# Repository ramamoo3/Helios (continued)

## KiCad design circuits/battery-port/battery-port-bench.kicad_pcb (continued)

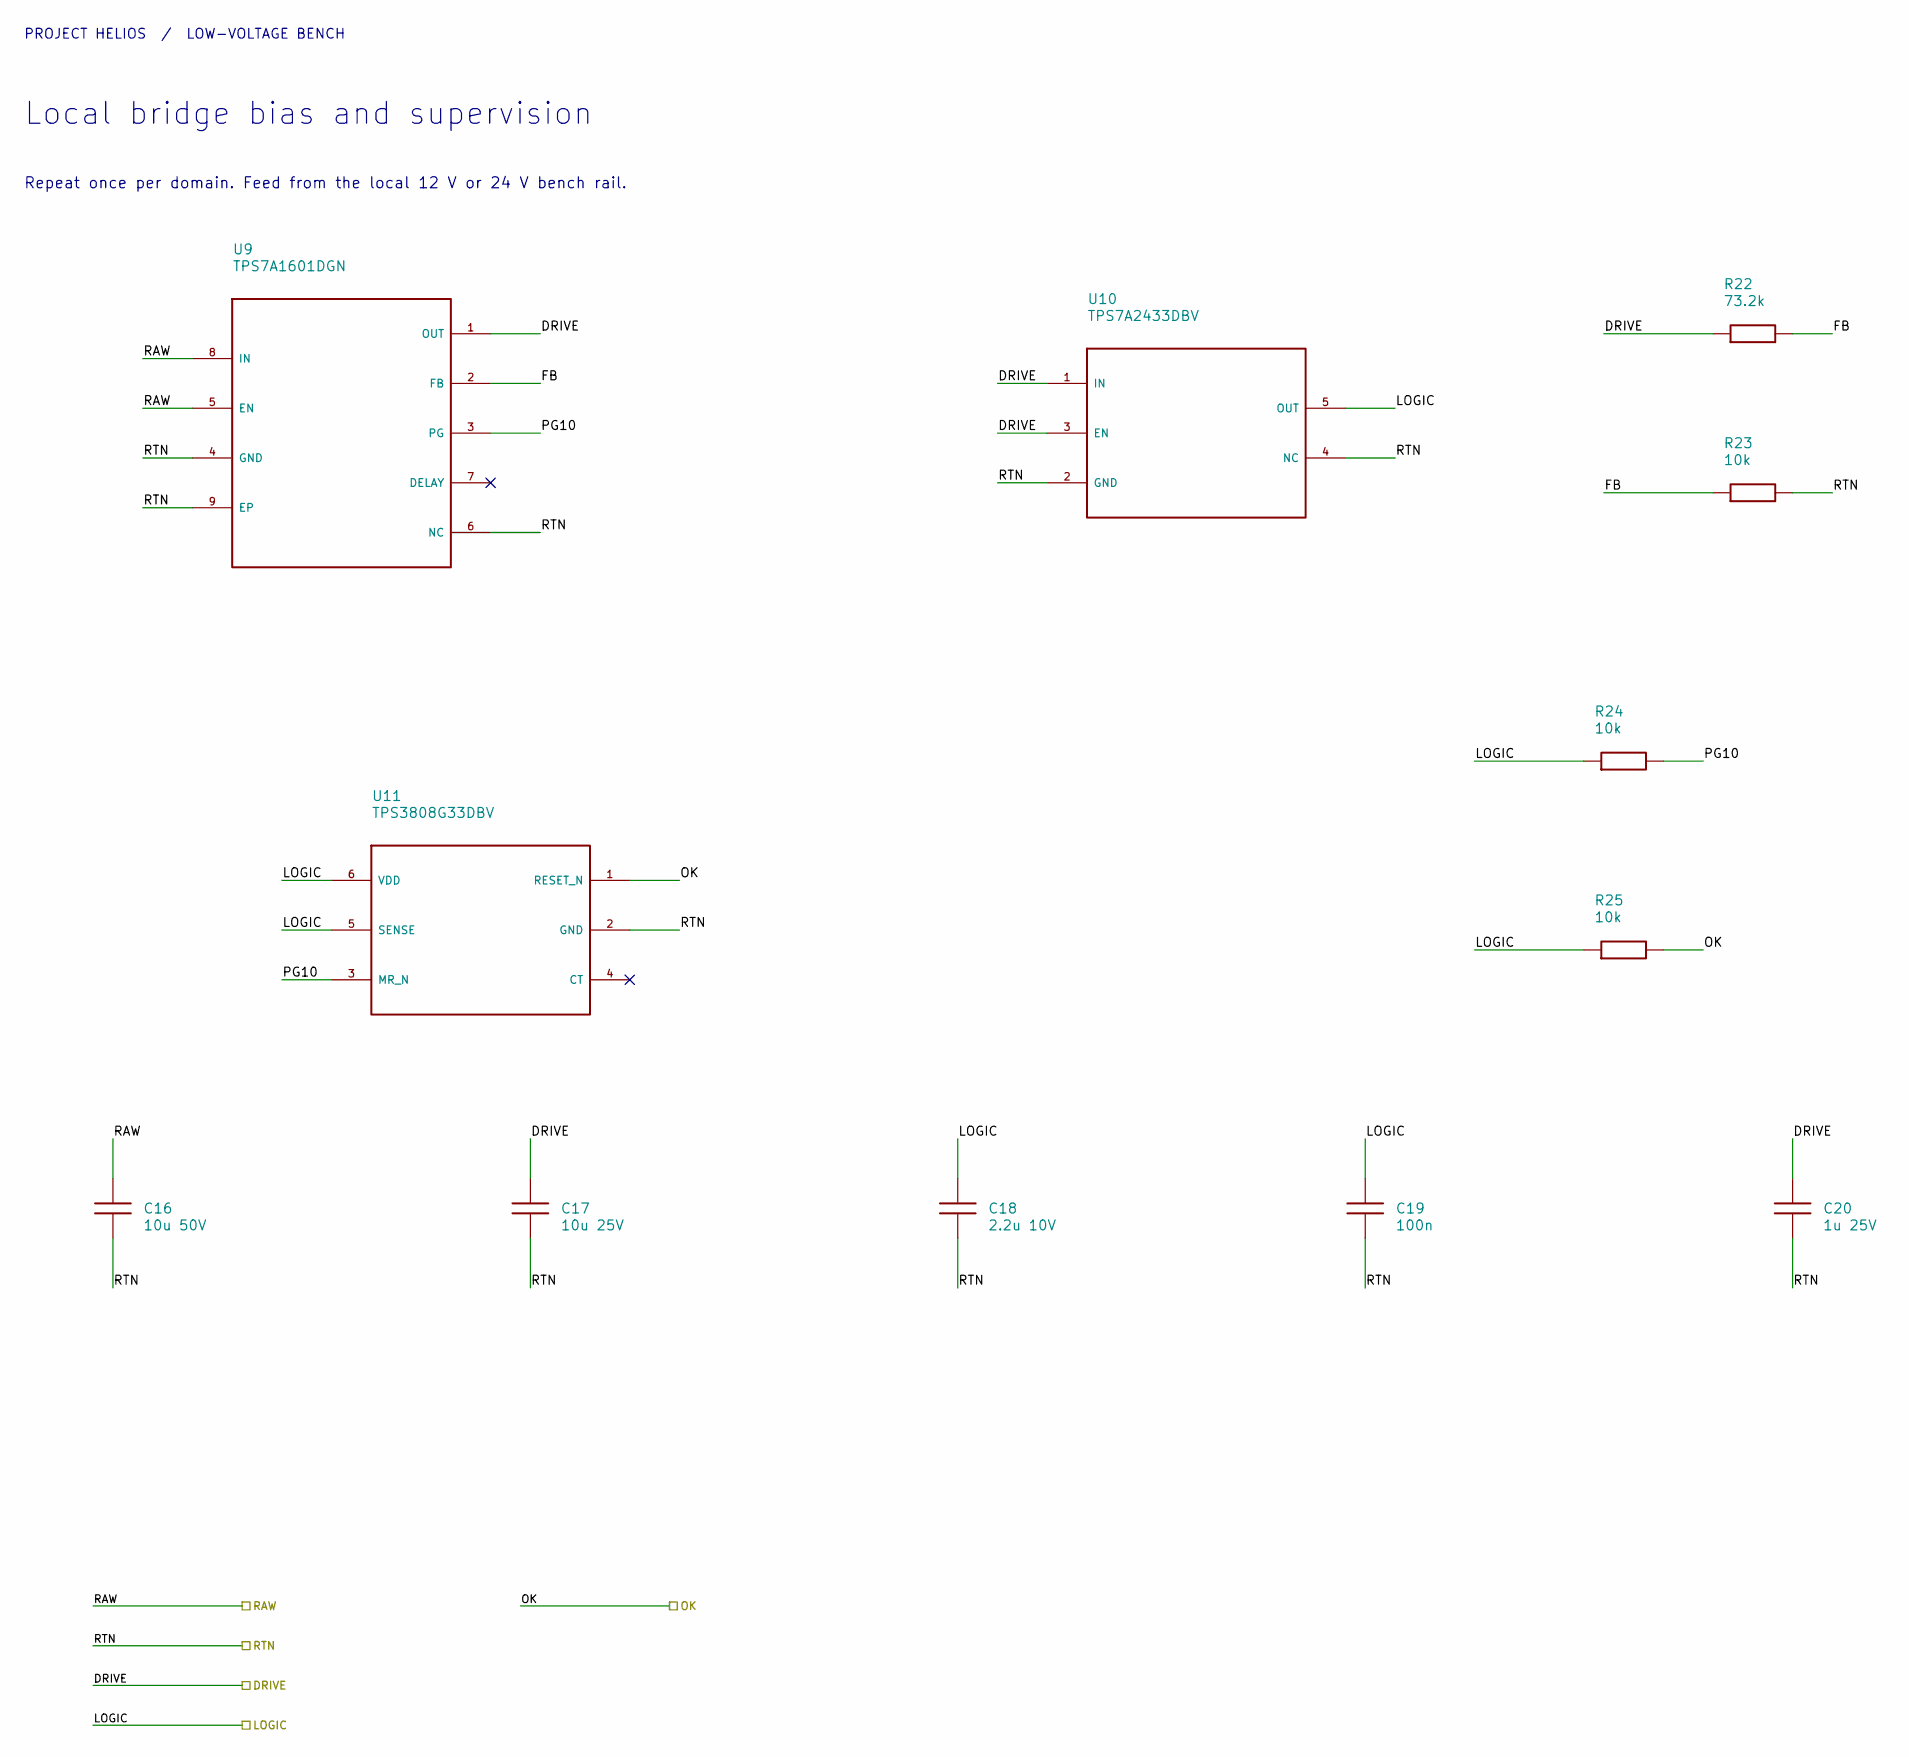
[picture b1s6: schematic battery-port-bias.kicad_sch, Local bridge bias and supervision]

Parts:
C16: 10u 50V; C_1206_3216Metric
C17: 10u 25V; C_1206_3216Metric
C18: 2.2u 10V; C_1206_3216Metric
C19: 100n; C_0805_2012Metric; Voltage Rating 50 V; MPN CGA4J2X8R1H104K125AA
C20: 1u 25V; C_0805_2012Metric
R22: 73.2k; R_0805_2012Metric
R23, R24, R25: 10k; R_0805_2012Metric
U9: TPS7A1601DGN; TI_DGN0008C
U10: TPS7A2433DBV; SOT-23-5
U11: TPS3808G33DBV; SOT-23-6

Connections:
/P0: C16.2, C17.2, C18.2, C19.2, C20.2, R23.2, U9.4 (GND), U9.6 (NC), U9.9 (EP), U10.2 (GND), U10.4 (NC), U11.2 (GND); also elsewhere on the board
/P3V3: C18.1, C19.1, R24.1, R25.1, U10.5 (OUT), U11.5 (SENSE), U11.6 (VDD); also elsewhere on the board
/P10: C17.1, C20.1, R22.1, U9.1 (OUT), U10.1 (IN), U10.3 (EN); also elsewhere on the board
/PACK12: C16.1, U9.5 (EN), U9.8 (IN); also elsewhere on the board
/PRI_OK: R25.2, U11.1 (RESET_N); also elsewhere on the board
/Primary bias/FB: R22.2, R23.1, U9.2 (FB)
/Primary bias/PG10: R24.2, U9.3 (PG), U11.3 (MR_N)

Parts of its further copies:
C116: 10u 50V; C_1206_3216Metric
C117: 10u 25V; C_1206_3216Metric
C118: 2.2u 10V; C_1206_3216Metric
C119: 100n; C_0805_2012Metric; Voltage Rating 50 V; MPN CGA4J2X8R1H104K125AA
C120: 1u 25V; C_0805_2012Metric
R122: 73.2k; R_0805_2012Metric
R123, R124, R125: 10k; R_0805_2012Metric
U109: TPS7A1601DGN; TI_DGN0008C
U110: TPS7A2433DBV; SOT-23-5
U111: TPS3808G33DBV; SOT-23-6

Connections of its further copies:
/LINK24: C116.1, U109.5 (EN), U109.8 (IN); also elsewhere on the board
/S0: C116.2, C117.2, C118.2, C119.2, C120.2, R123.2, U109.4 (GND), U109.6 (NC), U109.9 (EP), U110.2 (GND), U110.4 (NC), U111.2 (GND); also elsewhere on the board
/S3V3: C118.1, C119.1, R124.1, R125.1, U110.5 (OUT), U111.5 (SENSE), U111.6 (VDD); also elsewhere on the board
/S10: C117.1, C120.1, R122.1, U109.1 (OUT), U110.1 (IN), U110.3 (EN); also elsewhere on the board
/SEC_OK: R125.2, U111.1 (RESET_N); also elsewhere on the board
/Secondary bias/FB: R122.2, R123.1, U109.2 (FB)
/Secondary bias/PG10: R124.2, U109.3 (PG), U111.3 (MR_N)

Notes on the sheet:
PROJECT HELIOS / LOW-VOLTAGE BENCH
Local bridge bias and supervision
Repeat once per domain. Feed from the local 12 V or 24 V bench rail.

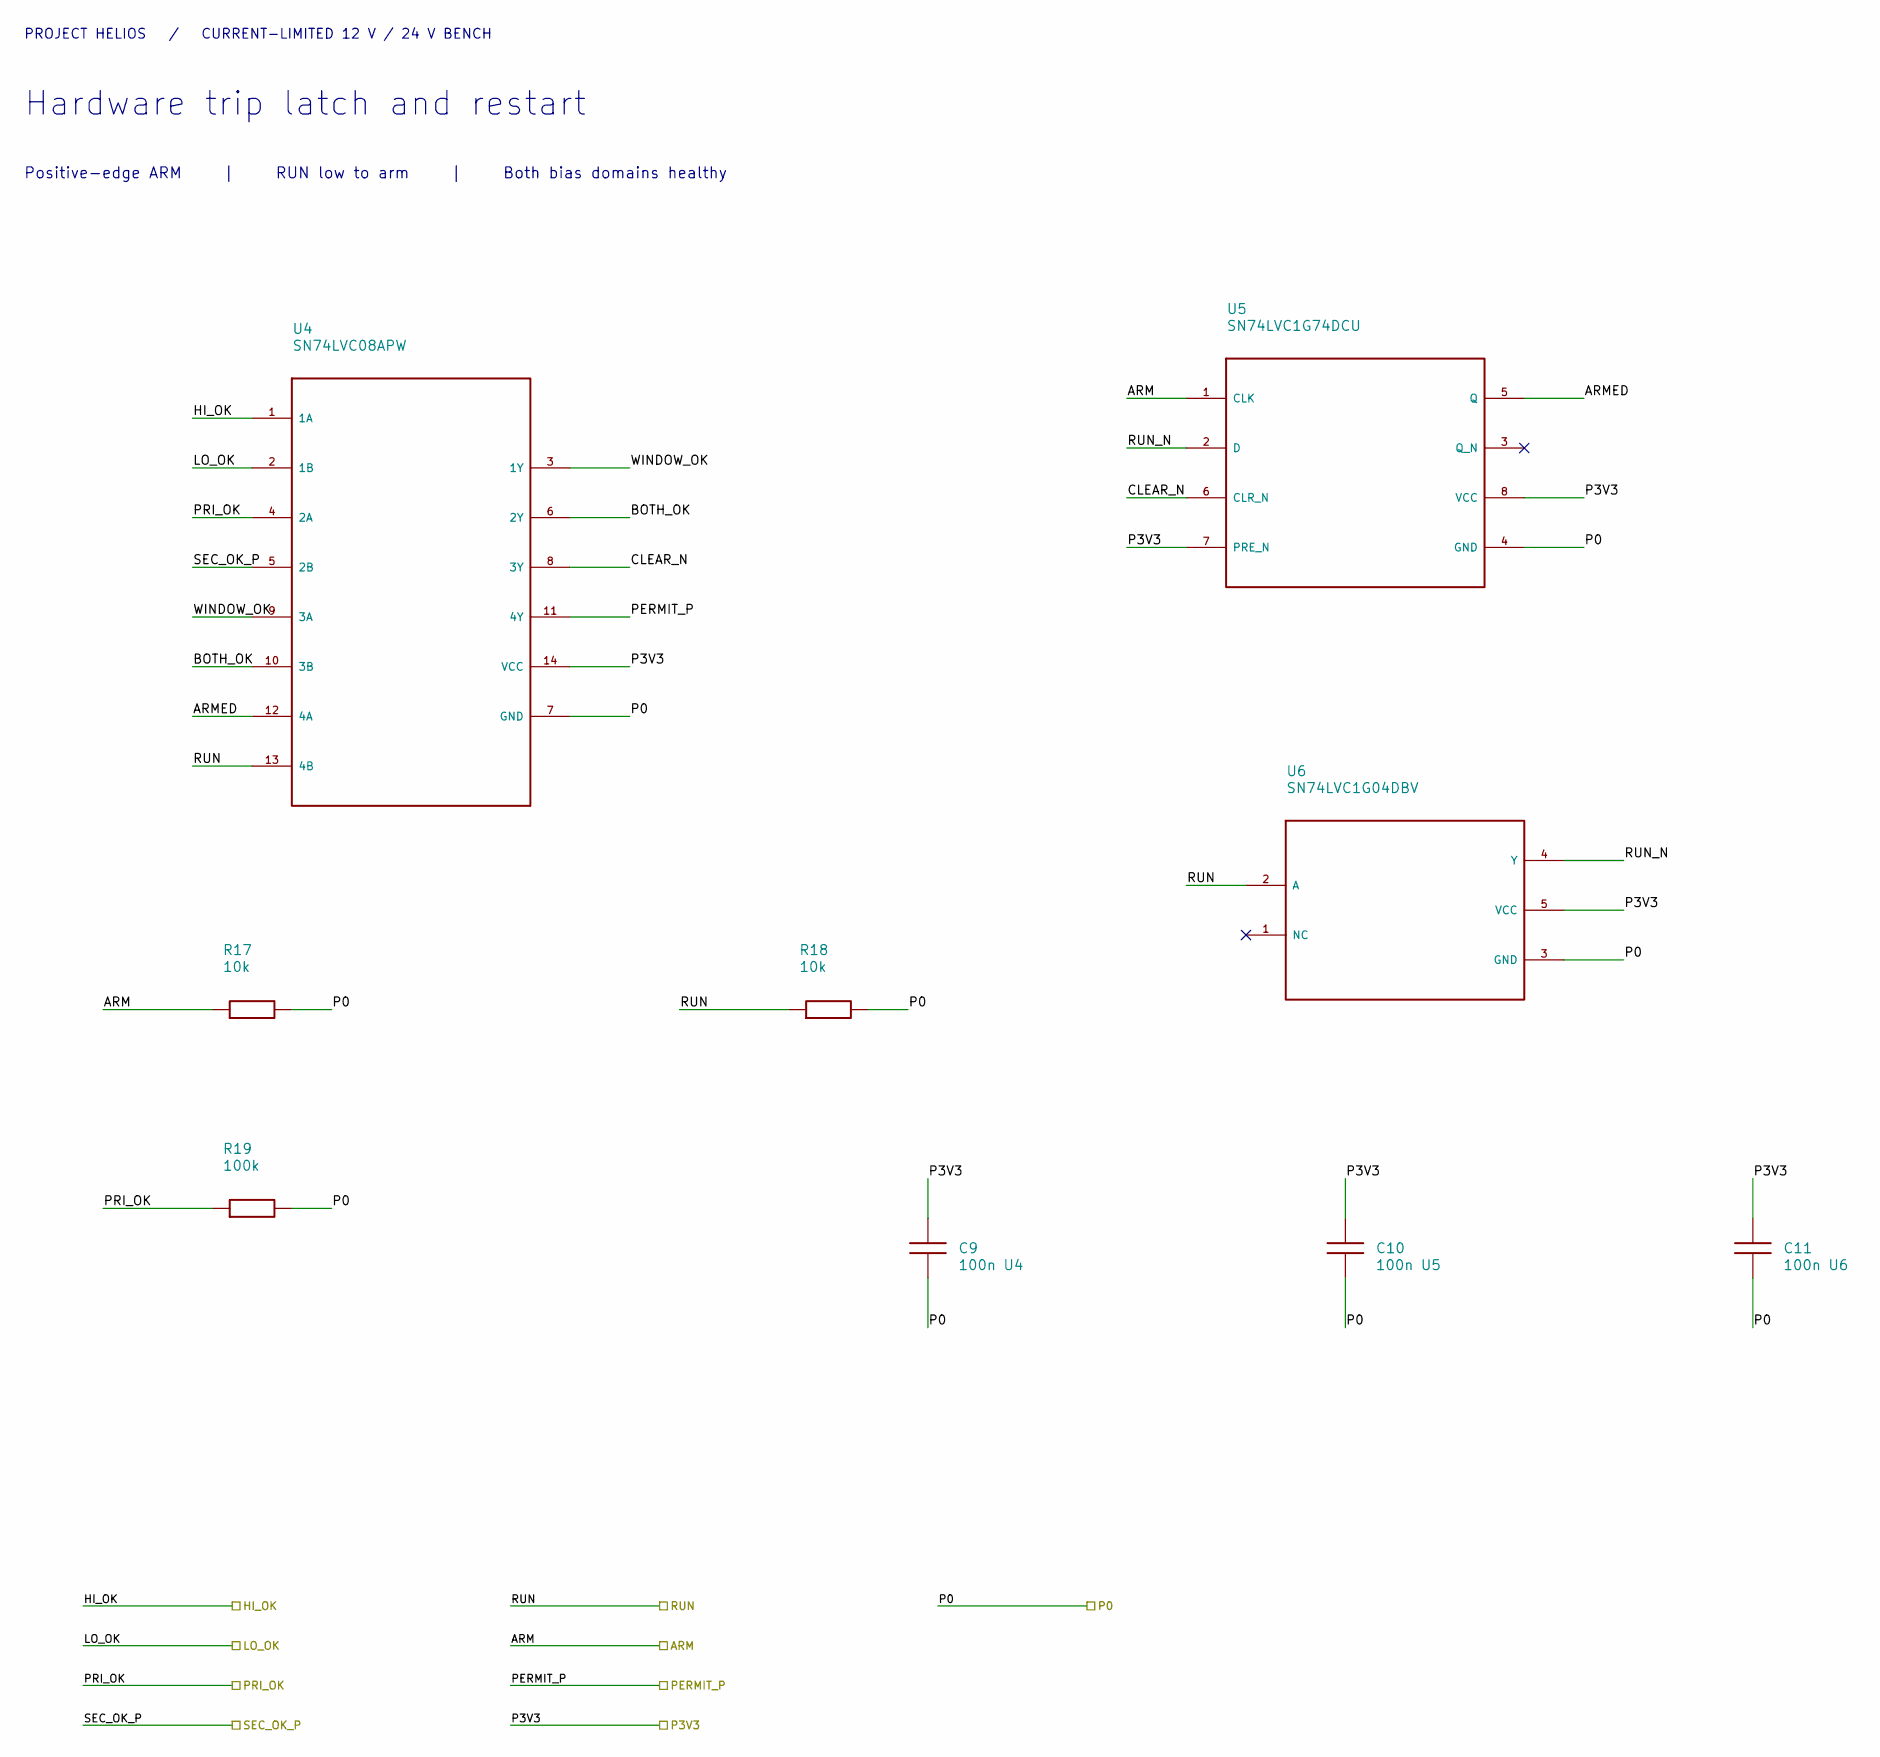
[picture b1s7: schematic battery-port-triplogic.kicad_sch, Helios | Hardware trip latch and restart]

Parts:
C9: 100n U4; C_0805_2012Metric
C10: 100n U5; C_0805_2012Metric
C11: 100n U6; C_0805_2012Metric
R17, R18: 10k; R_0805_2012Metric
R19: 100k; R_0805_2012Metric
U4: SN74LVC08APW; TSSOP-14_4.4x5mm_P0.65mm
U5: SN74LVC1G74DCU; TI_DCU0008A
U6: SN74LVC1G04DBV; SOT-23-5

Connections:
/ARM: R17.1, U5.1 (CLK); also elsewhere on the board
/HI_OK: U4.1 (1A); also elsewhere on the board
/LO_OK: U4.2 (1B); also elsewhere on the board
/Latch and re-arm/ARMED: U4.12 (4A), U5.5 (Q)
/Latch and re-arm/BOTH_OK: U4.6 (2Y), U4.10 (3B)
/Latch and re-arm/CLEAR_N: U4.8 (3Y), U5.6 (CLR_N)
/Latch and re-arm/RUN_N: U5.2 (D), U6.4 (Y)
/Latch and re-arm/WINDOW_OK: U4.3 (1Y), U4.9 (3A)
/P0: C9.2, C10.2, C11.2, R17.2, R18.2, R19.2, U4.7 (GND), U5.4 (GND), U6.3 (GND); also elsewhere on the board
/P3V3: C9.1, C10.1, C11.1, U4.14 (VCC), U5.7 (PRE_N), U5.8 (VCC), U6.5 (VCC); also elsewhere on the board
/PERMIT_P: U4.11 (4Y); also elsewhere on the board
/PRI_OK: R19.1, U4.4 (2A); also elsewhere on the board
/RUN: R18.1, U4.13 (4B), U6.2 (A); also elsewhere on the board
/SEC_OK_P: U4.5 (2B); also elsewhere on the board

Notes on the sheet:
PROJECT HELIOS / CURRENT-LIMITED 12 V / 24 V BENCH
Hardware trip latch and restart
Positive-edge ARM | RUN low to arm | Both bias domains healthy

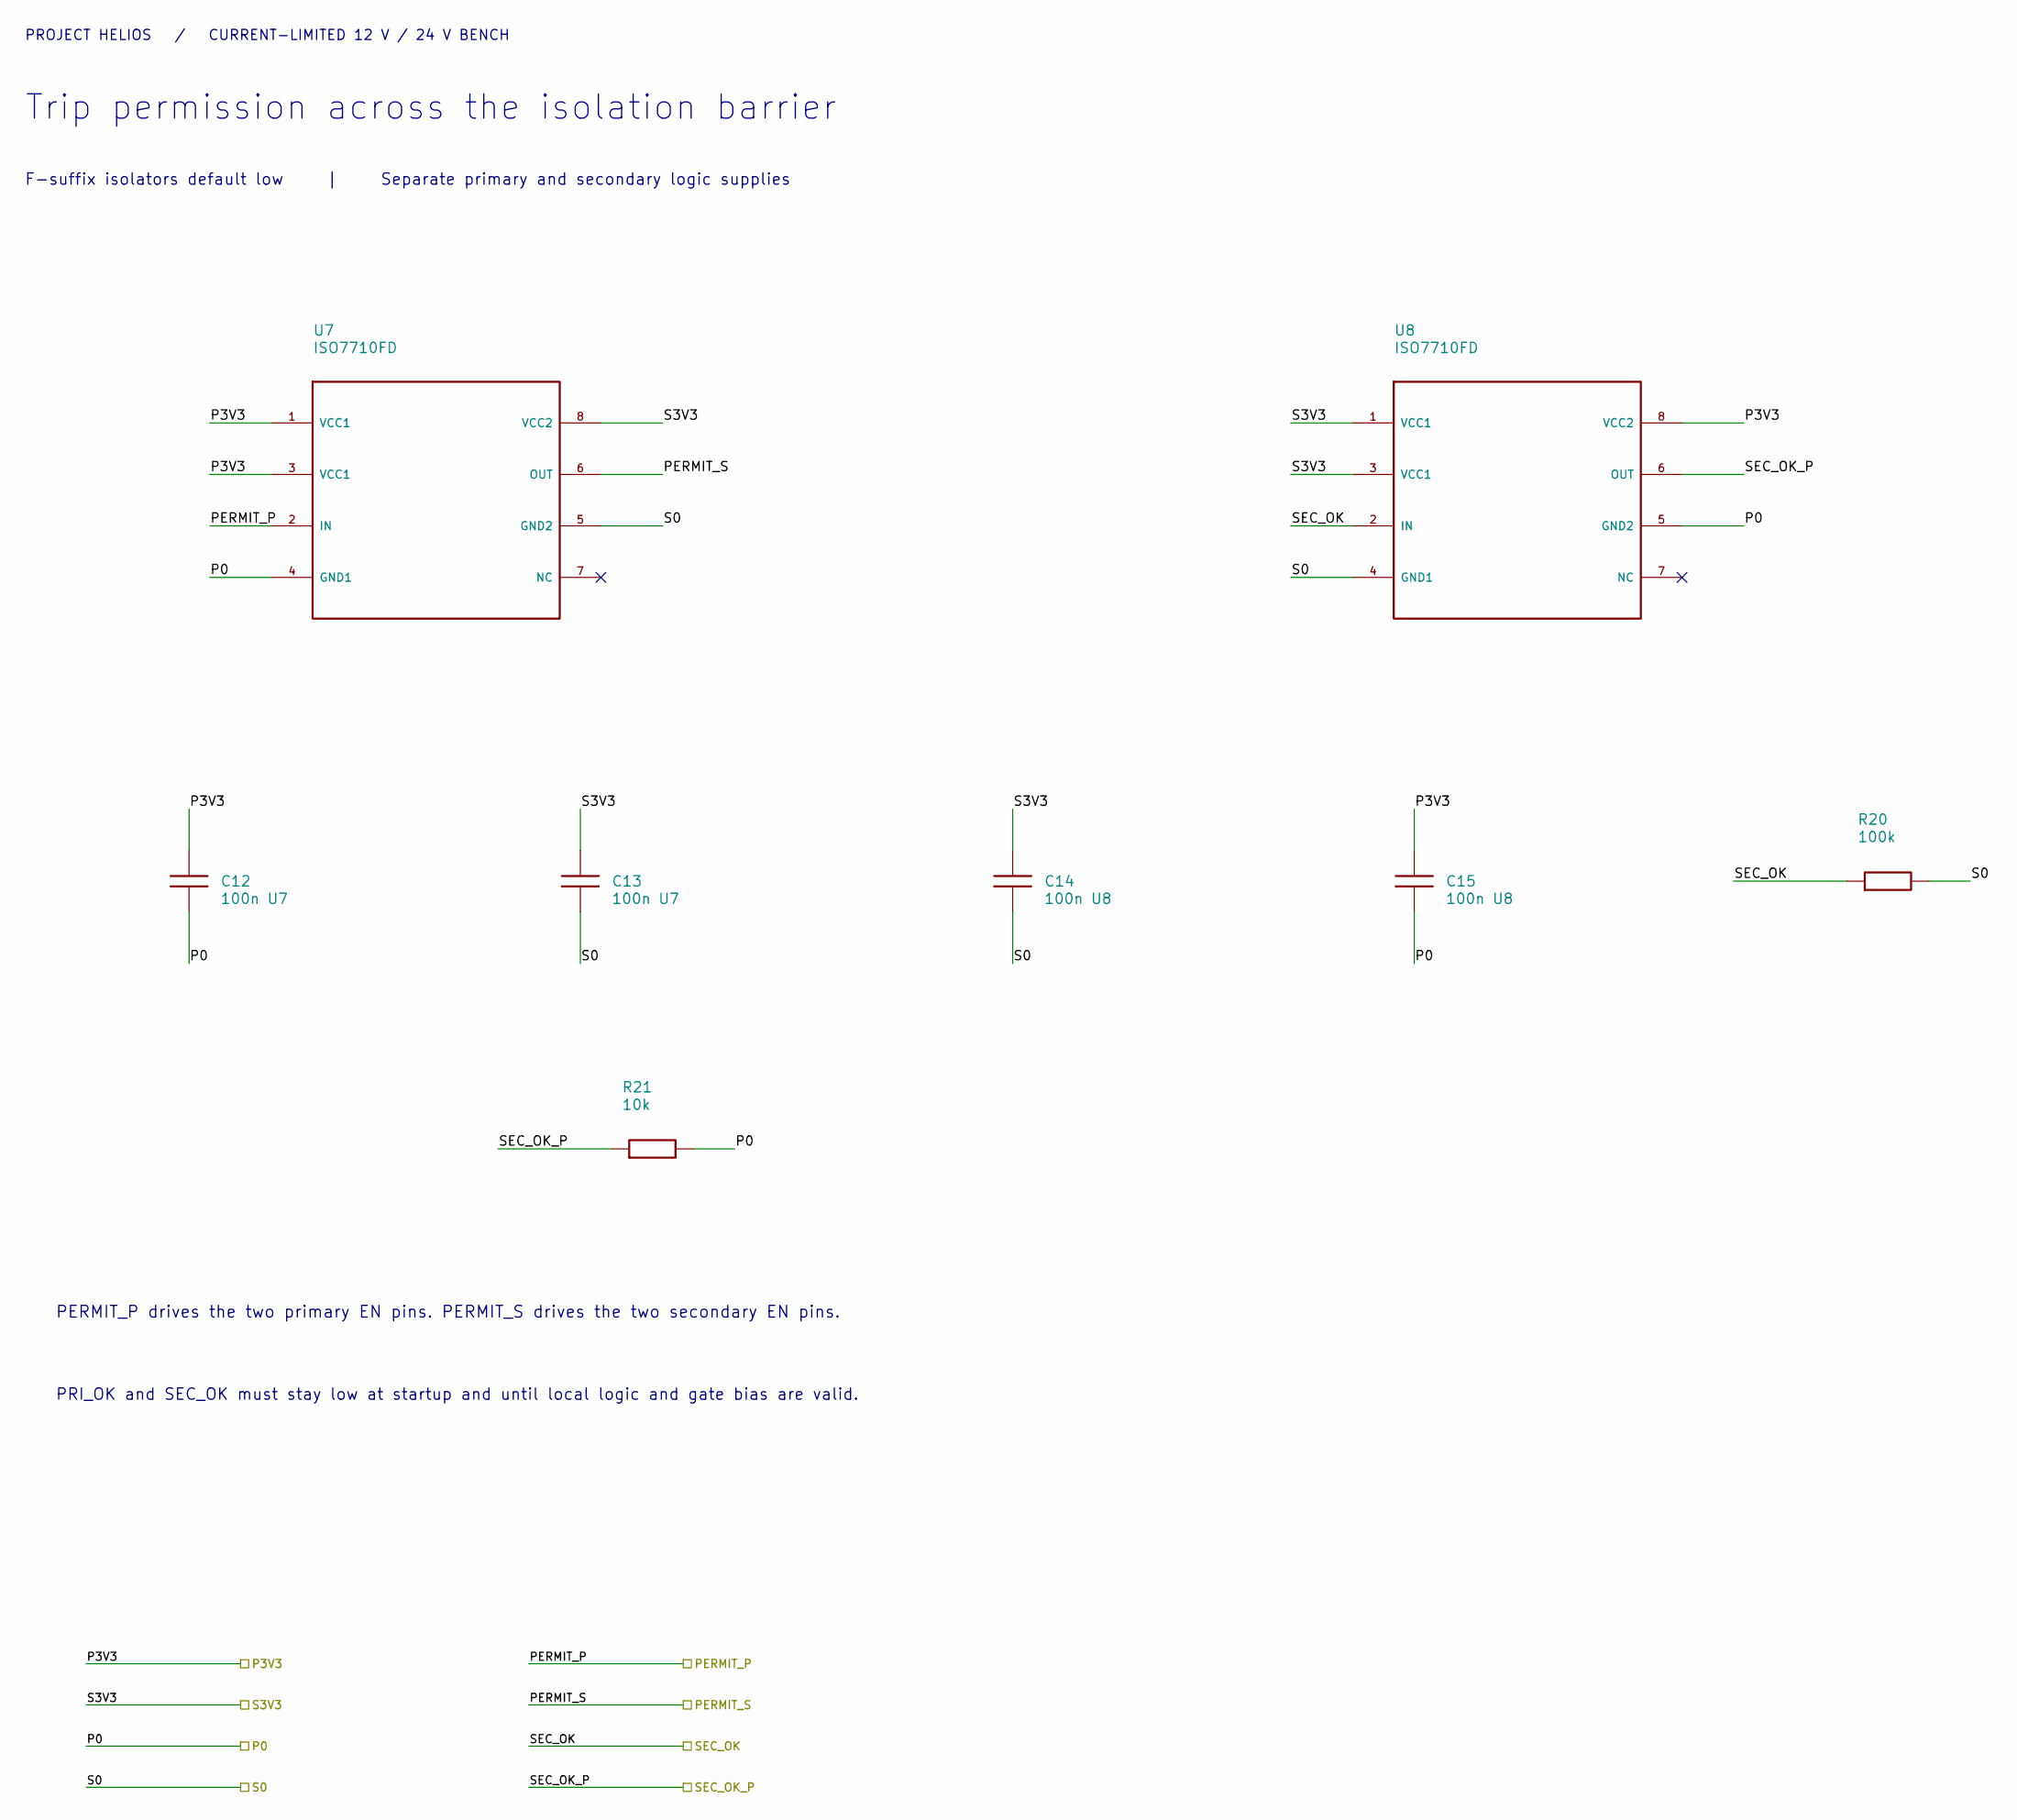
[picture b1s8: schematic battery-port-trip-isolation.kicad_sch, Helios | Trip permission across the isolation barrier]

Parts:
C12, C13: 100n U7; C_0805_2012Metric
C14, C15: 100n U8; C_0805_2012Metric
R20: 100k; R_0805_2012Metric
R21: 10k; R_0805_2012Metric
U7, U8: ISO7710FD; SOIC-8_3.9x4.9mm_P1.27mm

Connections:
/P0: C12.2, C15.2, R21.2, U7.4 (GND1), U8.5 (GND2); also elsewhere on the board
/P3V3: C12.1, C15.1, U7.1 (VCC1), U7.3 (VCC1), U8.8 (VCC2); also elsewhere on the board
/PERMIT_P: U7.2 (IN); also elsewhere on the board
/PERMIT_S: U7.6 (OUT); also elsewhere on the board
/S0: C13.2, C14.2, R20.2, U7.5 (GND2), U8.4 (GND1); also elsewhere on the board
/S3V3: C13.1, C14.1, U7.8 (VCC2), U8.1 (VCC1), U8.3 (VCC1); also elsewhere on the board
/SEC_OK: R20.1, U8.2 (IN); also elsewhere on the board
/SEC_OK_P: R21.1, U8.6 (OUT); also elsewhere on the board

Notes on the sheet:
PROJECT HELIOS / CURRENT-LIMITED 12 V / 24 V BENCH
Trip permission across the isolation barrier
F-suffix isolators default low | Separate primary and secondary logic supplies
PERMIT_P drives the two primary EN pins. PERMIT_S drives the two secondary EN pins.
PRI_OK and SEC_OK must stay low at startup and until local logic and gate bias are valid.

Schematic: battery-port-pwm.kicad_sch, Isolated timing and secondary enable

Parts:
C21, C22: 100n U12; C_0805_2012Metric
C23: 100n U13; C_0805_2012Metric
R26, R27, R28, R29: 10k; R_0805_2012Metric
U12: ISO7720FD; SOIC-8_3.9x4.9mm_P1.27mm
U13: SN74LVC1G08DBV; SOT-23-5

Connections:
/P0: C21.2, R26.2, R27.2, R28.2, R29.2, U12.4 (GND1); also elsewhere on the board
/P3V3: C21.1, U12.1 (VCC1); also elsewhere on the board
/PERMIT_S: U13.1 (A); also elsewhere on the board
/P_NEG: R27.1; also elsewhere on the board
/P_POS: R26.1; also elsewhere on the board
/S0: C22.2, C23.2, U12.5 (GND2), U13.3 (GND); also elsewhere on the board
/S3V3: C22.1, C23.1, U12.8 (VCC2), U13.5 (VCC); also elsewhere on the board
/SEC_EN: U13.4 (Y); also elsewhere on the board
/SEC_OK: U13.2 (B); also elsewhere on the board
/S_NEG: U12.6 (OUTB); also elsewhere on the board
/S_NEG_IN: R29.1, U12.3 (INB); also elsewhere on the board
/S_POS: U12.7 (OUTA); also elsewhere on the board
/S_POS_IN: R28.1, U12.2 (INA); also elsewhere on the board

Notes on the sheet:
PROJECT HELIOS / LOW-VOLTAGE BENCH
Isolated timing and secondary enable
Two phase-shifted timing signals cross from the primary controller. Both inputs low represents dead time.

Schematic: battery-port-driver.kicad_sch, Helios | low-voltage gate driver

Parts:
C4: 2.2u; C_1206_3216Metric; Voltage Rating 50 V; MPN C3216X7R1H225K160AB
C5, C6: 100n; C_0805_2012Metric; Voltage Rating 50 V; MPN CGA4J2X8R1H104K125AA
R6, R7: 4.7R; R_0805_2012Metric
R8, R9, R10: 10k; R_0805_2012Metric
U2: UCC27282DRC; VSON-10-1EP_3x3mm_P0.5mm_EP1.65x2.4mm

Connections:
/G1: R6.2, R8.1; also elsewhere on the board
/G2: R7.2, R9.1; also elsewhere on the board
/P0: C4.2, C5.2, R9.2, R10.2, U2.9 (VSS), U2.11 (EP); also elsewhere on the board
/P10: C4.1, C5.1, U2.1 (VDD); also elsewhere on the board
/PA_H: U2.7 (HI); also elsewhere on the board
/PA_L: U2.8 (LI); also elsewhere on the board
/PERMIT_P: R10.1, U2.6 (EN); also elsewhere on the board
/PRI_A: C6.2, R8.2, U2.5 (HS); also elsewhere on the board
/Primary A/BOOT: C6.1, U2.3 (HB)
/Primary A/HO_RAW: R6.1, U2.4 (HO)
/Primary A/LO_RAW: R7.1, U2.10 (LO)

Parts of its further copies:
C104, C204, C304: 2.2u; C_1206_3216Metric; Voltage Rating 50 V; MPN C3216X7R1H225K160AB
C105, C106, C205, C206, C305, C306: 100n; C_0805_2012Metric; Voltage Rating 50 V; MPN CGA4J2X8R1H104K125AA
R106, R107, R206, R207, R306, R307: 4.7R; R_0805_2012Metric
R108, R109, R110, R208, R209, R210, R308, R309, R310: 10k; R_0805_2012Metric
U102, U202, U302: UCC27282DRC; VSON-10-1EP_3x3mm_P0.5mm_EP1.65x2.4mm

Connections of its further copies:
/G3: R106.2, R108.1; also elsewhere on the board
/G4: R107.2, R109.1; also elsewhere on the board
/G5: R206.2, R208.1; also elsewhere on the board
/G6: R207.2, R209.1; also elsewhere on the board
/G7: R306.2, R308.1; also elsewhere on the board
/G8: R307.2, R309.1; also elsewhere on the board
/P0: C104.2, C105.2, R109.2, R110.2, U102.9 (VSS), U102.11 (EP); also elsewhere on the board
/P10: C104.1, C105.1, U102.1 (VDD); also elsewhere on the board
/PB_H: U102.7 (HI); also elsewhere on the board
/PB_L: U102.8 (LI); also elsewhere on the board
/PERMIT_P: R110.1, U102.6 (EN); also elsewhere on the board
/PRI_B: C106.2, R108.2, U102.5 (HS); also elsewhere on the board
/Primary B/BOOT: C106.1, U102.3 (HB)
/Primary B/HO_RAW: R106.1, U102.4 (HO)
/Primary B/LO_RAW: R107.1, U102.10 (LO)
/S0: C204.2, C205.2, C304.2, C305.2, R209.2, R210.2, R309.2, R310.2, U202.9 (VSS), U202.11 (EP), U302.9 (VSS), U302.11 (EP); also elsewhere on the board
/S10: C204.1, C205.1, C304.1, C305.1, U202.1 (VDD), U302.1 (VDD); also elsewhere on the board
/SA_H: U202.7 (HI); also elsewhere on the board
/SA_L: U202.8 (LI); also elsewhere on the board
/SB_H: U302.7 (HI); also elsewhere on the board
/SB_L: U302.8 (LI); also elsewhere on the board
/SEC_A: C206.2, R208.2, U202.5 (HS); also elsewhere on the board
/SEC_B: C306.2, R308.2, U302.5 (HS); also elsewhere on the board
/SEC_EN: R210.1, R310.1, U202.6 (EN), U302.6 (EN); also elsewhere on the board
/Secondary A/BOOT: C206.1, U202.3 (HB)
/Secondary A/HO_RAW: R206.1, U202.4 (HO)
/Secondary A/LO_RAW: R207.1, U202.10 (LO)
/Secondary B/BOOT: C306.1, U302.3 (HB)
/Secondary B/HO_RAW: R306.1, U302.4 (HO)
/Secondary B/LO_RAW: R307.1, U302.10 (LO)

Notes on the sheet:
PROJECT HELIOS / BATTERY PORT
Gate drive for one bench half-bridge
12 V / 24 V prototype | One instance per leg | 10 V local drive bias
Gate resistors and gate-to-source discharge paths
Local bias and bootstrap storage
Place C4 and C5 at VDD/VSS. Place C6 at HB/HS.
PERMIT is active high and is pulled low locally.
PWM_H and PWM_L require controller dead time.
SW returns to the high-side MOSFET source. DRV_0 returns to the low-side source.
Supply PWM and permission locally to each isolated bridge domain. Verify bootstrap charge before the first high-side pulse.

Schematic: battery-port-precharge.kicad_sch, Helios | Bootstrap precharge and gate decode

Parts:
C40, C41, C42, C43, C44, C45, C46, C47, C48, C49: 100n; C_0805_2012Metric; Voltage Rating 50 V; MPN CGA4J2X8R1H104K125AA
R40, R41, R42: 10k; R_0805_2012Metric
U40, U44: SN74LVC04APW; TSSOP-14_4.4x5mm_P0.65mm
U41, U45: SN74LVC86APW; TSSOP-14_4.4x5mm_P0.65mm
U42, U43, U46, U47: SN74LVC08APW; TSSOP-14_4.4x5mm_P0.65mm
U48: ISO7721FD; SOIC-8_3.9x4.9mm_P1.27mm

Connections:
/Bootstrap precharge and gate decode/PRE_S: U44.5 (3A), U45.1 (1A), U45.4 (2A), U48.6 (OUTB)
/Bootstrap precharge and gate decode/P_ACK: U43.8 (3Y), U43.12 (4A)
/Bootstrap precharge and gate decode/P_NN: U40.4 (2Y), U42.4 (2A), U42.10 (3B)
/Bootstrap precharge and gate decode/P_NP: U40.2 (1Y), U42.1 (1A), U42.13 (4B)
/Bootstrap precharge and gate decode/P_NPC: U40.6 (3Y), U43.2 (1B), U43.5 (2B)
/Bootstrap precharge and gate decode/P_NX: U42.11 (4Y), U43.4 (2A)
/Bootstrap precharge and gate decode/P_PX: U42.8 (3Y), U43.1 (1A)
/Bootstrap precharge and gate decode/P_XN: U41.3 (1Y), U42.2 (1B)
/Bootstrap precharge and gate decode/P_XP: U41.6 (2Y), U42.5 (2B)
/Bootstrap precharge and gate decode/S_ACK: U47.8 (3Y), U47.12 (4A)
/Bootstrap precharge and gate decode/S_LOCAL_ACK: U47.11 (4Y), U48.7 (INA)
/Bootstrap precharge and gate decode/S_NN: U44.4 (2Y), U46.4 (2A), U46.10 (3B)
/Bootstrap precharge and gate decode/S_NP: U44.2 (1Y), U46.1 (1A), U46.13 (4B)
/Bootstrap precharge and gate decode/S_NPC: U44.6 (3Y), U47.2 (1B), U47.5 (2B)
/Bootstrap precharge and gate decode/S_NX: U46.11 (4Y), U47.4 (2A)
/Bootstrap precharge and gate decode/S_PX: U46.8 (3Y), U47.1 (1A)
/Bootstrap precharge and gate decode/S_XN: U45.3 (1Y), U46.2 (1B)
/Bootstrap precharge and gate decode/S_XP: U45.6 (2Y), U46.5 (2B)
/P0: C40.2, C41.2, C42.2, C43.2, C48.2, R40.2, R41.2, R42.2, U40.7 (GND), U40.9 (4A), U40.11 (5A), U40.13 (6A), U41.7 (GND), U41.9 (3A), U41.10 (3B), U41.12 (4A), U41.13 (4B), U42.7 (GND), U43.7 (GND), U48.4 (GND1); also elsewhere on the board
/P3V3: C40.1, C41.1, C42.1, C43.1, C48.1, U40.14 (VCC), U41.14 (VCC), U42.14 (VCC), U43.14 (VCC), U48.1 (VCC1); also elsewhere on the board
/PA_H: U43.3 (1Y); also elsewhere on the board
/PA_L: U42.3 (1Y), U43.9 (3A); also elsewhere on the board
/PB_H: U43.6 (2Y); also elsewhere on the board
/PB_L: U42.6 (2Y), U43.10 (3B); also elsewhere on the board
/PERMIT_P: U43.13 (4B); also elsewhere on the board
/PRE_ACK_P: R41.1, U43.11 (4Y); also elsewhere on the board
/PRE_ACK_S: R42.1, U48.2 (OUTA); also elsewhere on the board
/PRE_REQ: R40.1, U40.5 (3A), U41.1 (1A), U41.4 (2A), U48.3 (INB); also elsewhere on the board
/P_NEG: U40.3 (2A), U41.2 (1B), U42.12 (4A); also elsewhere on the board
/P_POS: U40.1 (1A), U41.5 (2B), U42.9 (3A); also elsewhere on the board
/S0: C44.2, C45.2, C46.2, C47.2, C49.2, U44.7 (GND), U44.9 (4A), U44.11 (5A), U44.13 (6A), U45.7 (GND), U45.9 (3A), U45.10 (3B), U45.12 (4A), U45.13 (4B), U46.7 (GND), U47.7 (GND), U48.5 (GND2); also elsewhere on the board
/S3V3: C44.1, C45.1, C46.1, C47.1, C49.1, U44.14 (VCC), U45.14 (VCC), U46.14 (VCC), U47.14 (VCC), U48.8 (VCC2); also elsewhere on the board
/SA_H: U47.3 (1Y); also elsewhere on the board
/SA_L: U46.3 (1Y), U47.9 (3A); also elsewhere on the board
/SB_H: U47.6 (2Y); also elsewhere on the board
/SB_L: U46.6 (2Y), U47.10 (3B); also elsewhere on the board
/SEC_EN: U47.13 (4B); also elsewhere on the board
/S_NEG: U44.3 (2A), U45.2 (1B), U46.12 (4A); also elsewhere on the board
/S_POS: U44.1 (1A), U45.5 (2B), U46.9 (3A); also elsewhere on the board

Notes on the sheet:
Primary gate decoder
Secondary gate decoder
Precharge request and acknowledgement across barrier
Ground unused inputs. Hardware permit independently disables the gate drivers.

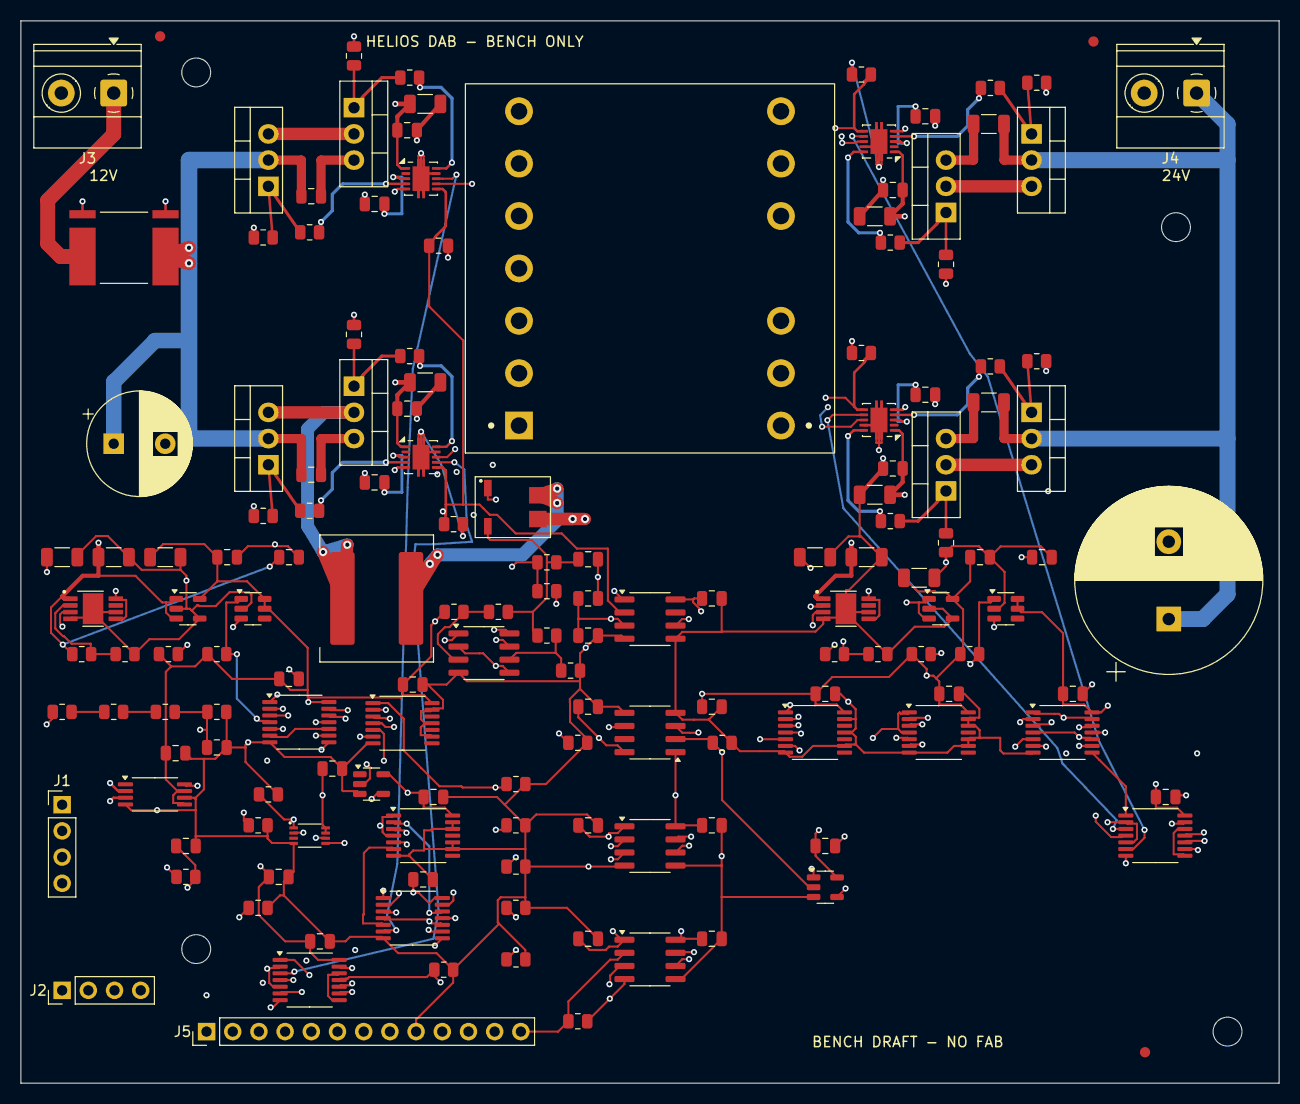
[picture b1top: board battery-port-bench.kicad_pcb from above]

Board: 4 copper layers, 122.0 x 103.0 mm, 156 parts (0 on the bottom side), 101 nets.

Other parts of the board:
FID1, FID2, FID3: Bench_fiducial_1mm
H1, H2, H3, H4: Bench_mount_M2_5
